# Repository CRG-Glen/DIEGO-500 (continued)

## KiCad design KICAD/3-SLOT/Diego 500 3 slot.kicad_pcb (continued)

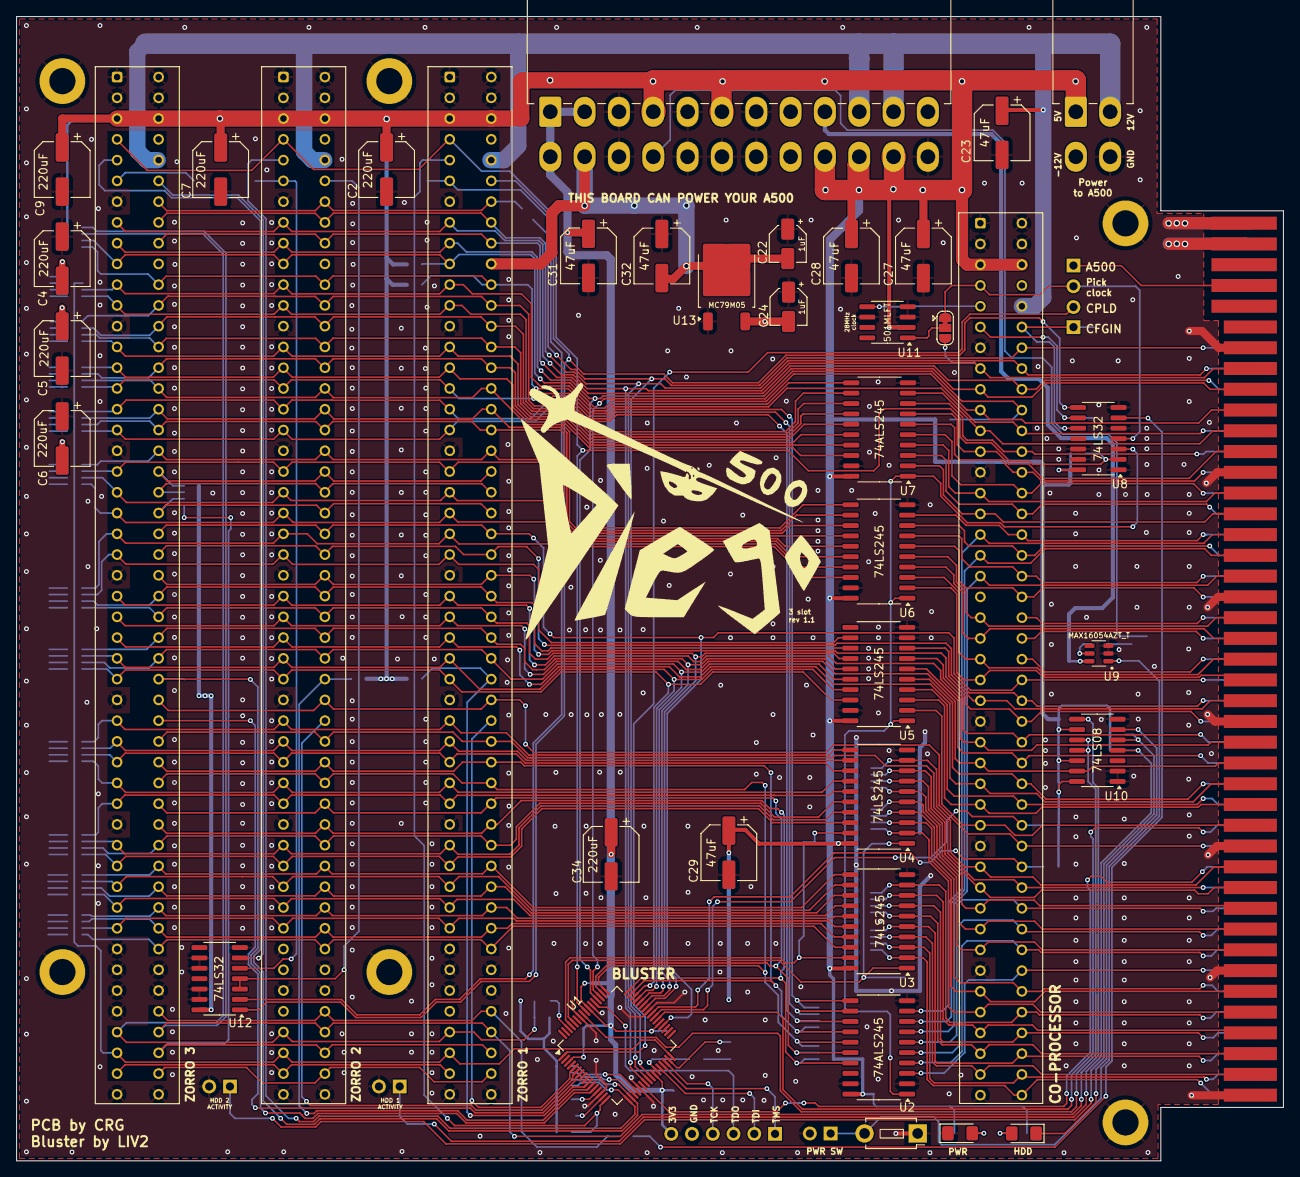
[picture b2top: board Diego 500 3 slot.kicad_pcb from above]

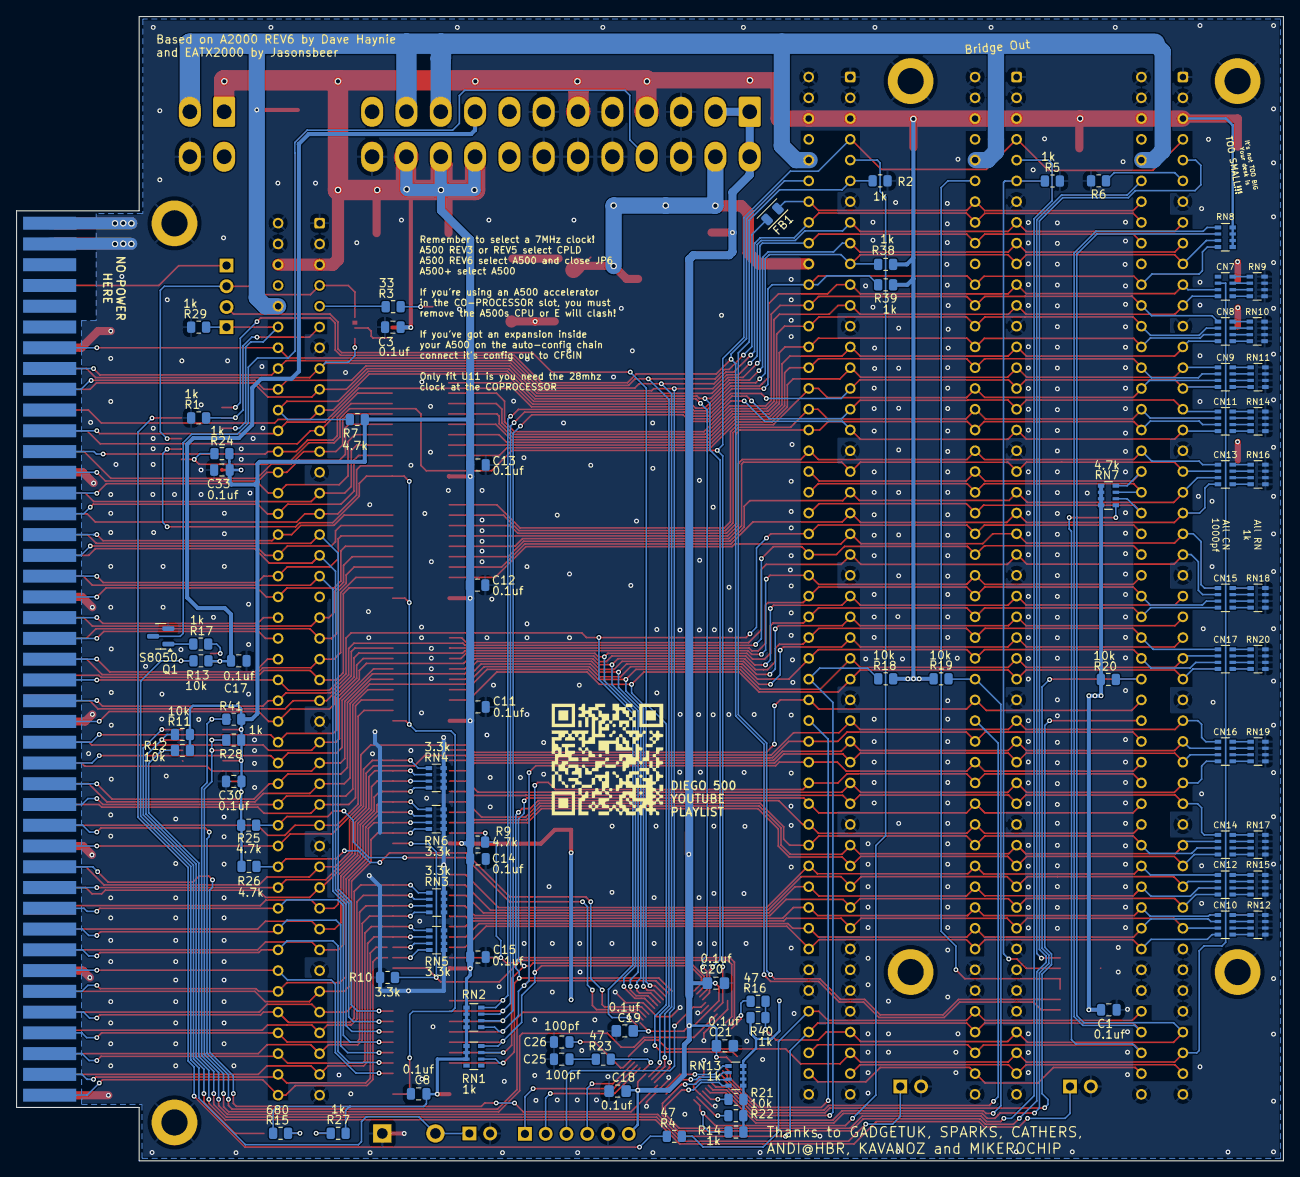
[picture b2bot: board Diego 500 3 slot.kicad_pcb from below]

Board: 4 copper layers, 155.0 x 140.0 mm, 133 parts (82 on the bottom side), 225 nets.

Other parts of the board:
R38, R39, R40, R41: 1k; R_0805_2012Metric

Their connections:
+5V: R38.1, R39.1, R40.1, R41.1; also elsewhere on the board
DOE: R40.2; also elsewhere on the board
_BusRST: R41.2; also elsewhere on the board
_INT2: R38.2; also elsewhere on the board
_INT6: R39.2; also elsewhere on the board

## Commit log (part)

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2026-02-25 Revise README for DIEGO 500 project
    Updated README to improve clarity and add information about the DIEGO 500 project.
2026-02-25 Revise README for DIEGO 500 project
    Updated README to include new project details and structure.
2026-02-27 3 slot added
2026-02-27 General update
2026-03-06 Fix autoconfig error
2026-03-06 Revise README for DIEGO 500 project
    Updated README to reflect project details and licensing.
2026-03-06 Revise README for DIEGO 500 project
    Updated README.md to improve formatting and clarity.
2026-03-06 License updated
    Updated the license from CERN Open Hardware License to Creative Commons Attribution-NonCommercial-ShareAlike 4.0 International Public License.
2026-03-06 Revise README for DIEGO 500
    Updated README to include project details and assembly instructions.
2026-03-06 License updated
    Updated the license from Creative Commons Attribution-NonCommercial-ShareAlike 4.0 to CERN Open Hardware Licence, including definitions and conditions for use, modification, and distribution.
2026-04-16 Update README with project details and FAQs
2026-04-21 KICAD and JLC files updated
2026-04-23 Revise CERN Open Hardware Licence text
    Updated the CERN Open Hardware Licence to reflect the correct variant and made various clarifications throughout the text.
2026-04-23 Revise LICENSE.md
    Updated definitions and clauses in the CERN-OHL-S License.
2026-04-23 Revise README for DIEGO 500 version 1.1
    Updated README to reflect version 1.1 changes, including ordering details, assembly instructions, and additional FAQs.
2026-04-27 Base 3D files added
2026-04-27 Revise README for DIEGO 500 project
    Updated README to include additional details about the DIEGO 500 project, including assembly instructions, testing results, and licensing information.
